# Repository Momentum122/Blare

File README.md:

# BLARE
 Blare is a four key alarm clock powered by XIAO ESP32 , a 3.3V piezo buzzer, a 2.25in TFT Screen and a custom PCB built with Onshape(for Case) , Vs code (for readme and BOM) , Kicad (for pcb) and Arduino Ide (for firmware) and also with the help of Hackclub's guide (https://blare.hackclub.com/docs/getting-started) 

#  Features
- Key 1 - Mode button 
  Three modes are there . Normal mode , set alarm hour , set alarm minute.
- Key 2 - Increase Button
  Increase the hours or minutes . 
- Key 3 - Decrease Button
  Decrease the hours or minutes .
- key 4 -
 It has 3 things to do . 
  When alarm is ringing it turns it off.
  When in normal mode turns alarm on or off.
  when in setting alarm mode it acts as a confirm button.
 When alarm is ringing it display WAKE UP

# File structure 
 - CAD  ( contains .step files for 3d models of the case).
 - Firmware contains the firmware code.
 - Images contains Images
 - PCB contains PCB files
 - Production contains files that are to be used to create hardware.
 - BOM.csv contains bill of materials.
 - README.md what you are reading right now .

# How to make
 - Order the PCB from a pcb manufacter ( i will use JLCPCB)
 - 3D print the case 
 - Flash the the XIAO with the firmware code 
 - and assemble all of the things .

# How to flash 
 - Detailed guide on https://wiki.seeedstudio.com/XIAO_ESP32C3_Getting_Started/

# BUILT WITH 
 - KICAD ( PCB )
 - Onshape ( case )
 - Arduino IDE ( firmware)

# ACKNOWLEDGEMENTS 
 - Built for Stardance Hackclub
 - Funded and built by the support of Hackclub
 - Thanks to Hackclub for providing resources and grants 
 - I dont anything used in this build except PCB , Case and firmware however feel free to use them however you like without restrictions.
 - Usage of AI for guidance in firmware and debuggin a few PCB errors.

Questions , Issues and complaints are accepted . If you have any contact me on my email.
EmaiL :- mandeepswami2010@gmail.com

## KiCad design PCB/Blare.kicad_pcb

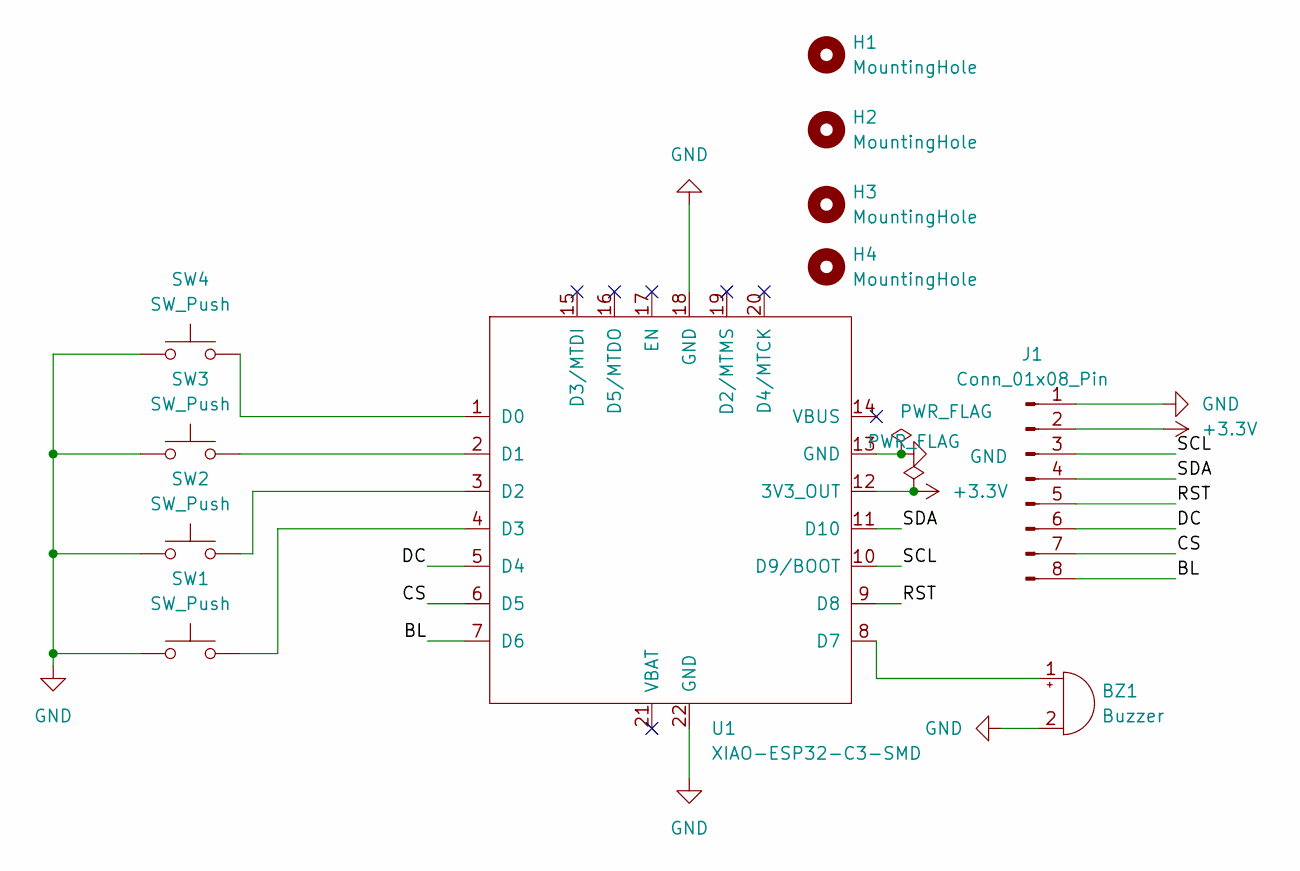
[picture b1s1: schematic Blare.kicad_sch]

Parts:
BZ1: Buzzer; Buzzer_12x9.5RM7.6
H1, H2, H3, H4: MountingHole; MountingHole_3.2mm_M3
J1: Conn_01x08_Pin; PinSocket_1x08_P2.54mm_Vertical
SW1, SW2, SW3, SW4: SW_Push; SW_Cherry_MX_1.00u_PCB
U1: XIAO-ESP32-C3-SMD; XIAO-ESP32-C3-DIP-SMD

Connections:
+3.3V: J1.2, U1.12 (3V3_OUT)
/BL: J1.8, U1.7 (D6)
/CS: J1.7, U1.6 (D5)
/DC: J1.6, U1.5 (D4)
/RST: J1.5, U1.9 (D8)
/SCL: J1.3, U1.10 (D9/BOOT)
/SDA: J1.4, U1.11 (D10)
GND: BZ1.2 (-), J1.1, SW1.1, SW2.1, SW3.1, SW4.1, U1.13 (GND), U1.18 (GND), U1.22 (GND)
unnamed: BZ1.1 (+), U1.8 (D7)
unnamed: SW4.2, U1.1 (D0)
unnamed: SW3.2, U1.2 (D1)
unnamed: SW2.2, U1.3 (D2)
unnamed: SW1.2, U1.4 (D3)

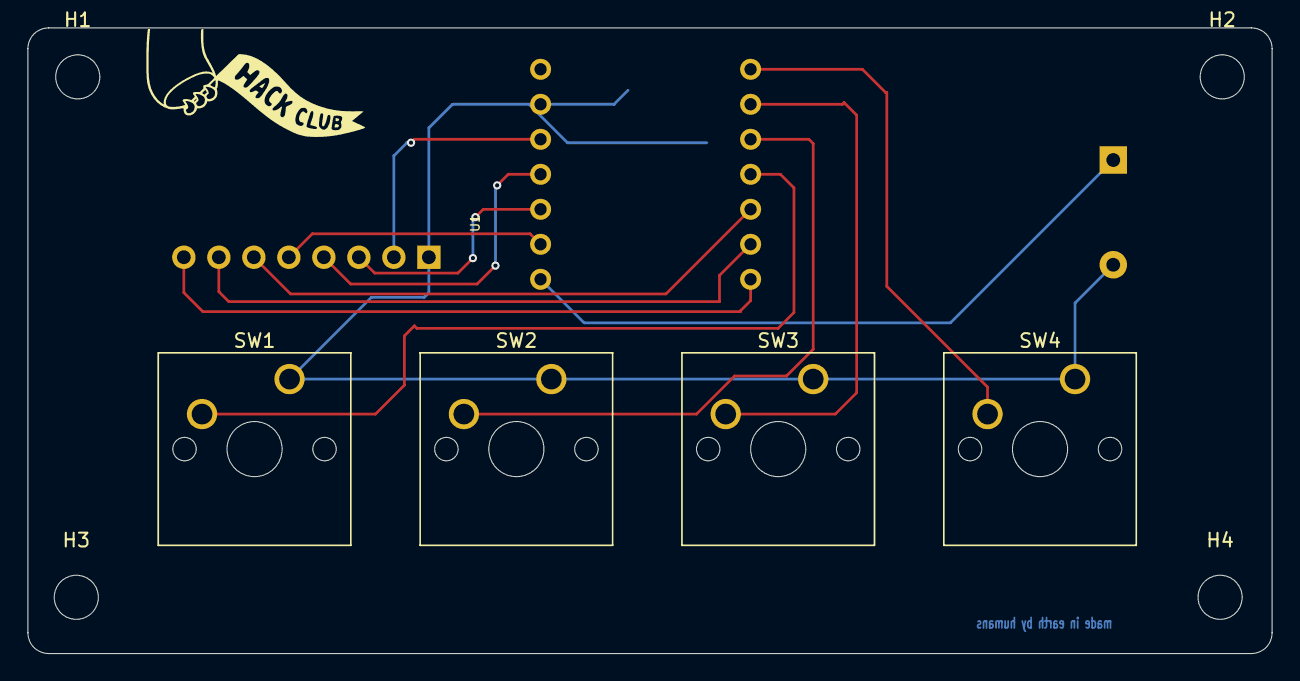
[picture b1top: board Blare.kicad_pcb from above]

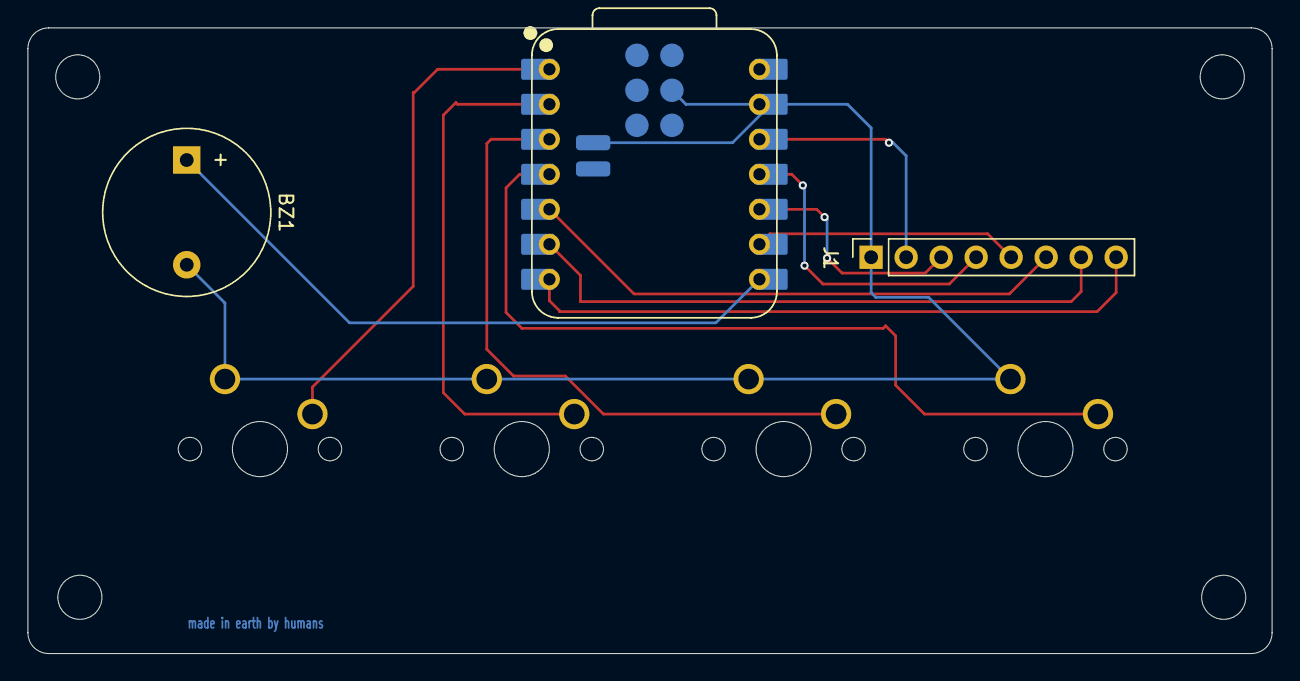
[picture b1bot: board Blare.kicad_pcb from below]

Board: 2 copper layers, 90.3 x 45.4 mm, 11 parts (3 on the bottom side), 13 nets.
